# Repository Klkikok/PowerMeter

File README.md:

# LPRS2_2023

Documentation link: https://docs.google.com/document/d/1wlLli0q4daZZRtQz-zDJgAOysabH1hmVt-DKWVhcbmg/edit#heading=h.j99920cq97rd

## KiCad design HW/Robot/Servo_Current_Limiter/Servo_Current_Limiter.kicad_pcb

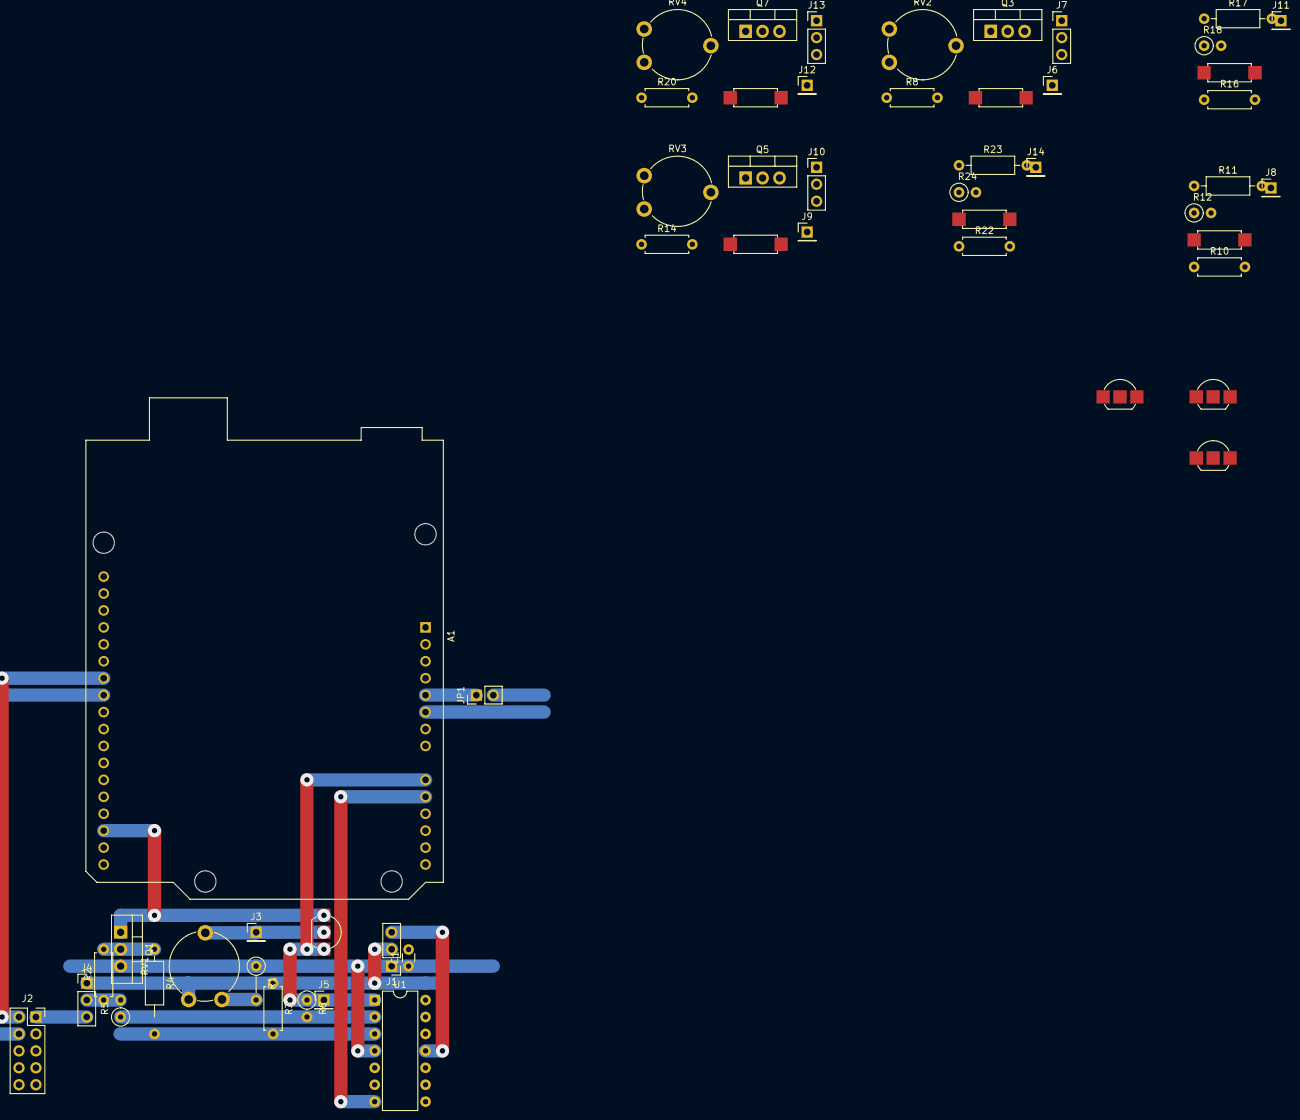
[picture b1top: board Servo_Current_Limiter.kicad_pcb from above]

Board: 2 copper layers, 54 parts (0 on the bottom side), 44 nets.

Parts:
A1: Arduino_UNO_R3; Arduino_UNO_R3_WithMountingHoles_Snapped_to_P2.54mm
C1: 100n; C_Disc_D3.0mm_W1.6mm_P2.50mm
J1, J4, J7, J10, J13: 1x3 2.54mm male; PinHeader_1x03_P2.54mm_Vertical
J2: Conn_02x05_Odd_Even; PinSocket_2x05_P2.54mm_Vertical
J3, J5, J6, J8, J9, J11, J12, J14: 1x1 2.54mm male; PinHeader_1x01_P2.54mm_Vertical
JP1: 1x2 2.54mm male; PinHeader_1x02_P2.54mm_Vertical
Q1, Q3, Q5, Q7: IRF4905; TO-220-3_Vertical
Q2, Q4, Q6, Q8: BC548; TO-92_Inline_inf
R1: 220; R_Axial_DIN0207_L6.3mm_D2.5mm_P5.08mm_Vertical
R2, R8, R14, R20: 0.1; R_Axial_DIN0207_L6.3mm_D2.5mm_P7.62mm_Horizontal
R3: 100k; R_Axial_DIN0207_L6.3mm_D2.5mm_P7.62mm_Horizontal
R4: 10k; R_Axial_DIN0207_L6.3mm_D2.5mm_P12.70mm_Horizontal
R5: 10k; R_Axial_DIN0207_L6.3mm_D2.5mm_P2.54mm_Vertical
R6, R12, R18, R24: 100k; R_Axial_DIN0207_L6.3mm_D2.5mm_P2.54mm_Vertical
R7, R13, R19: 220; R_Axial_DIN0207_L6.3mm_D2.5mm_Pinf_Horizontal
R9, R15, R21: 100k; R_Axial_DIN0207_L6.3mm_D2.5mm_Pinf_Horizontal
R10, R16, R22: 10k; R_Axial_DIN0207_L6.3mm_D2.5mm_P7.62mm_Horizontal
R11, R17, R23: 10k; R_Axial_DIN0207_L6.3mm_D2.5mm_P10.16mm_Horizontal
RV1, RV2, RV3, RV4: 250; Potentiometer_Piher_PT-10-V10_Vertical
U1: LM324; DIP-14_W7.62mm

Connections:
+5V: C1.1, J1.1, JP1.2 (B), Q1.3 (S), Q3.3 (S), Q5.3 (S), Q7.3 (S), R1.1, R7.1, R13.1, R19.1, U1.4 (V+)
-5V: C1.2, J1.3, U1.11 (V-)
/ARD_PWM0: A1.26 (D11), J2.2
/ARD_PWM1: A1.25 (D10), J2.4
/ARD_PWM2: A1.24 (D9), J2.6
/ARD_PWM3: A1.20 (D5), J2.8
/DIS0: A1.17 (D2), Q1.1 (G), Q2.1 (C)
/DIS1: Q3.1 (G), Q4.1 (C)
/DIS2: Q5.1 (G), Q6.1 (C)
/DIS3: Q7.1 (G), Q8.1 (C)
/OUT0: A1.9 (A0), J5.1, Q2.3 (E), R6.1, U1.1
/OUT1: A1.10 (A1), J8.1, Q4.3 (E), R12.1, U1.7
/OUT2: A1.11 (A2), J11.1, Q6.3 (E), R18.1, U1.8
/OUT3: A1.12 (A3), J14.1, Q8.3 (E), R24.1, U1.14
/PWM0: J2.1, J4.3
/PWM1: J2.3, J7.3
/PWM2: J2.5, J10.3
/PWM3: J2.7, J13.3
/ch0/N: J4.2, R2.1, R5.2
/ch0/P: Q1.2 (D), R2.2, R4.1
/ch1/N: J7.2, R8.1, R11.2
/ch1/P: Q3.2 (D), R8.2, R10.1
/ch2/N: J10.2, R14.1, R17.2
/ch2/P: Q5.2 (D), R14.2, R16.1
/ch3/N: J13.2, R20.1, R23.2
/ch3/P: Q7.2 (D), R20.2, R22.1
GND: A1.6 (GND), A1.7 (GND), J1.2, J2.9, J2.10, J4.1, J7.1, J10.1, J13.1, R3.1, R9.1, R15.1, R21.1, RV1.3, RV2.3, RV3.3, RV4.3
unnamed: A1.5 (+5V), JP1.1 (A)
unnamed: J3.1, Q2.2 (B), RV1.2
unnamed: J6.1, Q4.2 (B), RV2.2
unnamed: J9.1, Q6.2 (B), RV3.2
unnamed: J12.1, Q8.2 (B), RV4.2
unnamed: R1.2, RV1.1
unnamed: R3.2, R4.2, U1.3 (+)
unnamed: R5.1, R6.2, U1.2 (-)
unnamed: R7.2, RV2.1
unnamed: R9.2, R10.2, U1.5 (+)
unnamed: R11.1, R12.2, U1.6 (-)
unnamed: R13.2, RV3.1
unnamed: R15.2, R16.2, U1.10 (+)
unnamed: R17.1, R18.2, U1.9 (-)
unnamed: R19.2, RV4.1
unnamed: R21.2, R22.2, U1.12 (+)
unnamed: R23.1, R24.2, U1.13 (-)

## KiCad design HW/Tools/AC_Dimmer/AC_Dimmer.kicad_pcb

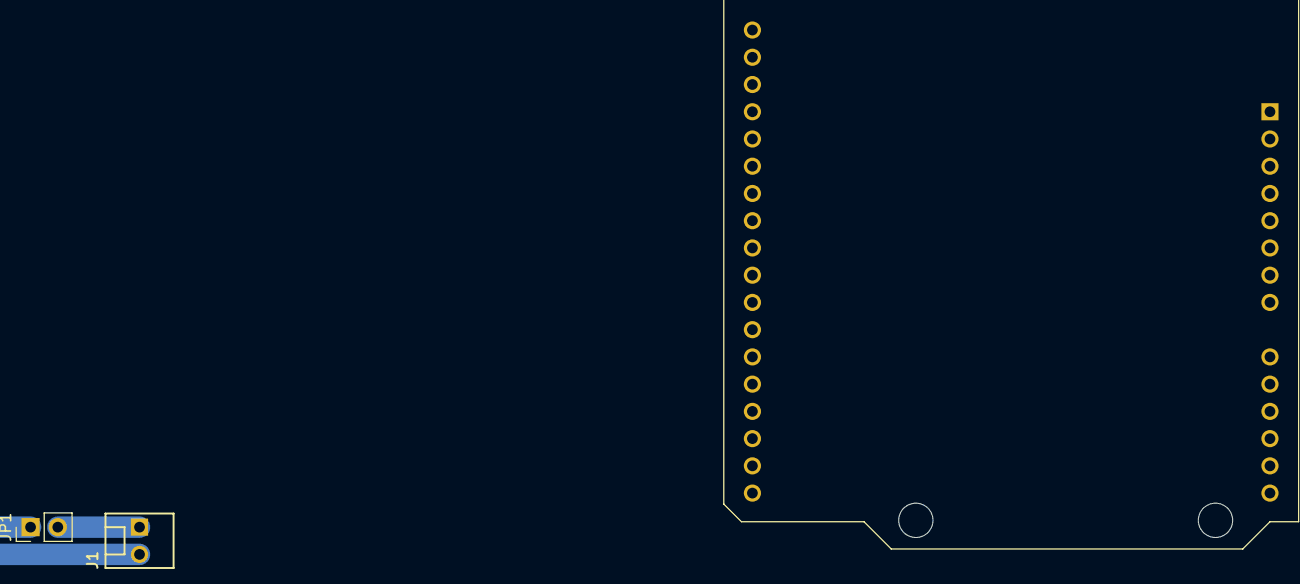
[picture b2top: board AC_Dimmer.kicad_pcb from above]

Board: 2 copper layers, 3 parts (0 on the bottom side), 3 nets.

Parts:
A1: Arduino_UNO_R3; Arduino_UNO_R3_WithMountingHoles_Snapped_to_P2.54mm
J1: 1x2 2.54mm male; MOLEX-22-23-2021
JP1: 1x2 2.54mm male; PinHeader_1x02_P2.54mm_Vertical

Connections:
+5V: J1.1, JP1.2 (B)
GND: A1.6 (GND), A1.7 (GND), J1.2
unnamed: A1.5 (+5V), JP1.1 (A)

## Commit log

2023-05-30 ADC reader
    Reading gnd, 3.3V and 5V using IRQ
2023-05-30 Packet struct added
    Added a struct in which we will put the read values and we need to the sending of the packet
2023-06-12 Little changes
2023-06-14 Final commit
2023-06-14 Added presentation video
2023-06-14 Update README.md
    Added documentation link
